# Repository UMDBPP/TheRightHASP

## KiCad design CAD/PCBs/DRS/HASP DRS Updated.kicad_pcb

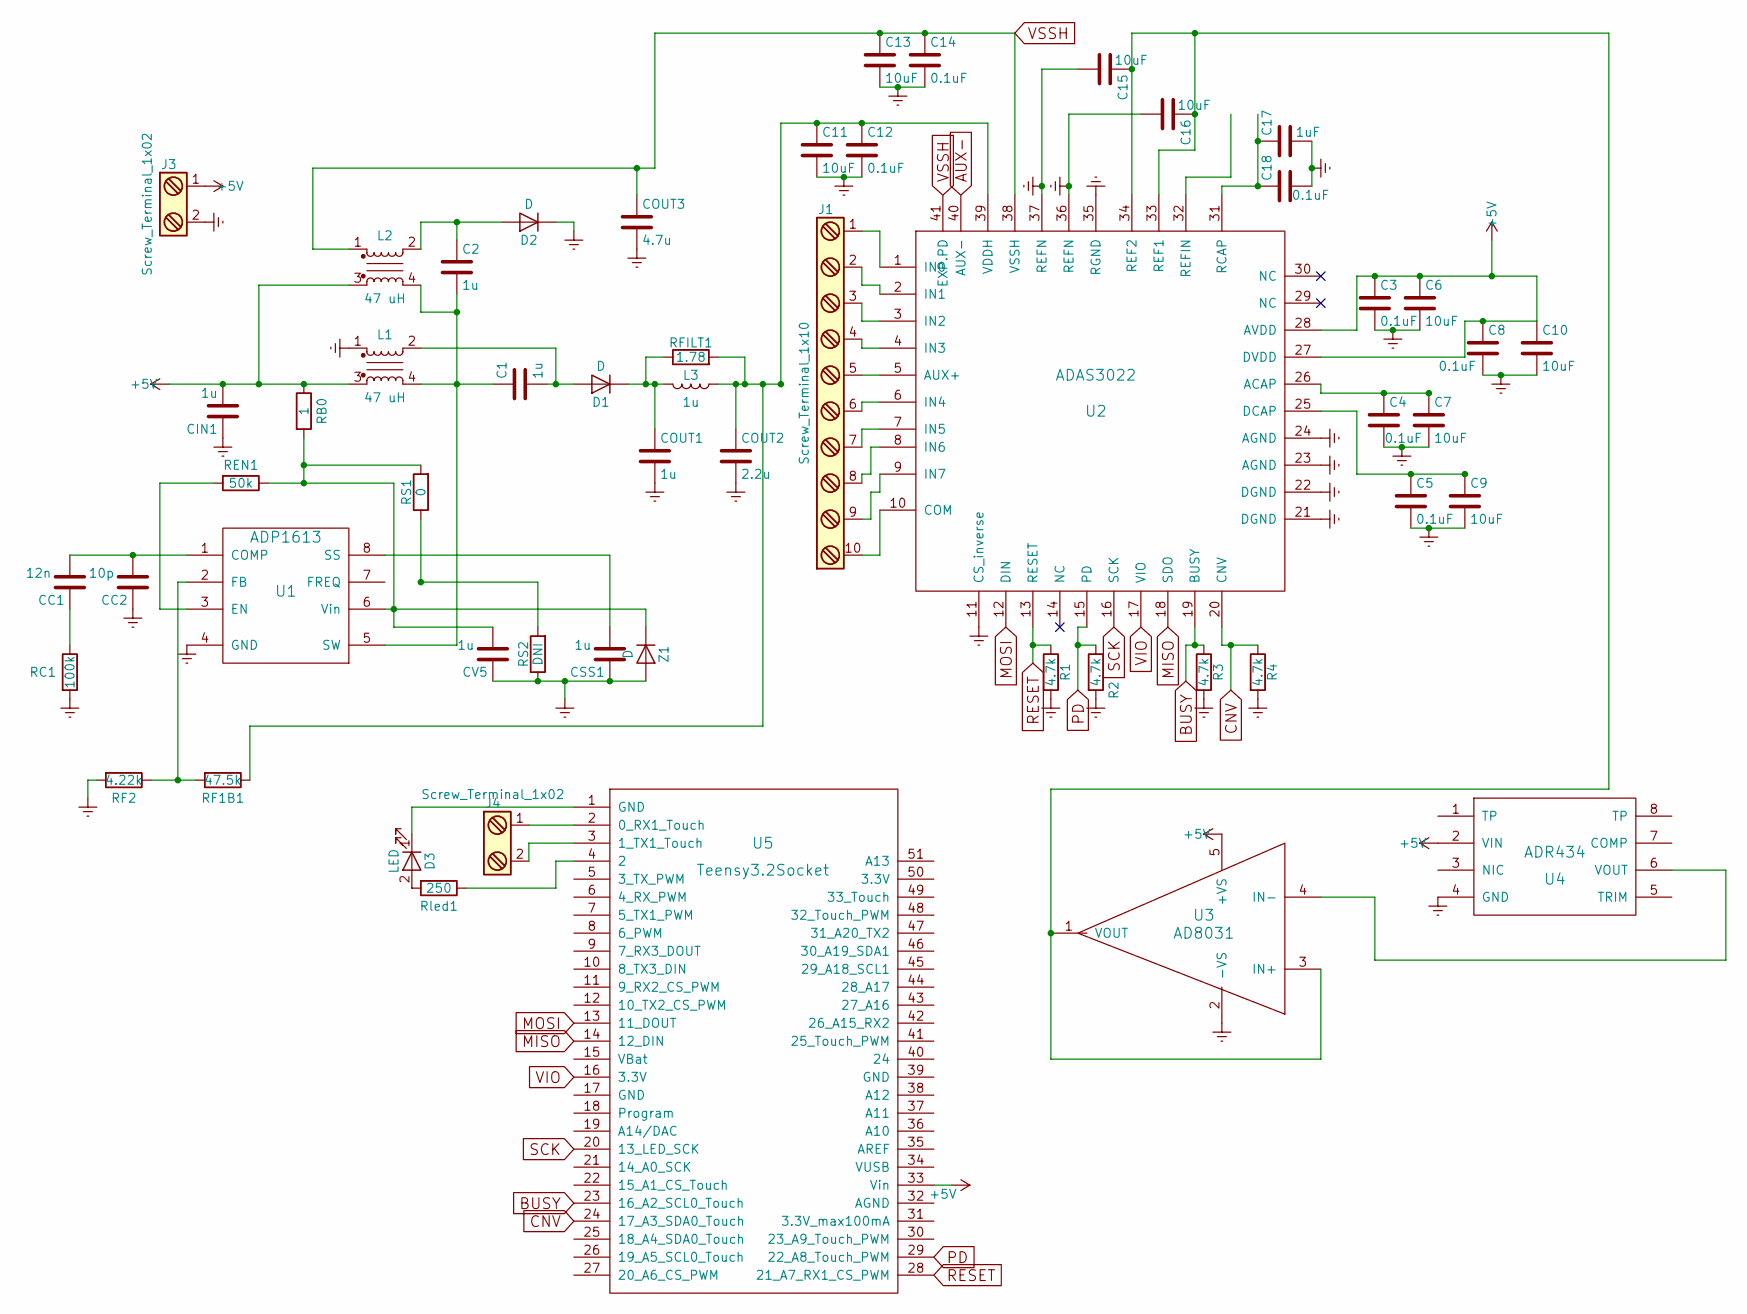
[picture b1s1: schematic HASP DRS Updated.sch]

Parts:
C1: 1u; C_0603
C2: 1u; C_0805
C3, C4, C5, C8, C12, C14, C18: 0.1uF; C_0603
C6, C7, C9, C10, C11, C13, C15, C16: 10uF; C_0603
C17: 1uF; C_0603
CC1: 12n; C_0603
CC2: 10p; C_0603
CIN1: 1u; C_0603
COUT1: 1u; C_0603
COUT2: 2.2u; C_1206
COUT3: 4.7u; C_1206
CSS1: 1u; C_0603
CV5: 1u; C_0603
D1, D2: D; D_SOT-23_ANK
D3: LED; LED_0603
J1: Screw_Terminal_1x10; TerminalBlock_Pheonix_MPT-2.54mm_10pol
J3, J4: Screw_Terminal_1x02; TerminalBlock_Pheonix_MPT-2.54mm_2pol
L1, L2: 47 uH; LPD5030-473MRB
L3: 1u; Neosid_Inductor_SM-NE30_SMD1210
R1, R2, R3, R4: 4.7k; R_0603
RB0: 1; R_0603
RC1: 100k; R_0603
REN1: 50k; R_0805
RF1B1: 47.5k; R_0603
RF2: 4.22k; R_0603
RFILT1: 1.78; R_0603
RS1: 0; R_0603
RS2: DNI; R_0603
Rled1: 250; R_0603
U1: ADP1613; SOP65P490X110-8N
U2: ADAS3022
U3: AD8031
U4: ADR434; SOIC127P600X175-8N
U5: Teensy3.2Socket
Z1: D; D_SOT-23_ANK

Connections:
AUX-: U2.40 (AUX-)
BUSY: R3.1, U2.19 (BUSY), U5.23 (16_A2_SCL0_Touch)
CNV: R4.1, U2.20 (CNV), U5.24 (17_A3_SDA0_Touch)
Earth: C3.2, C4.2, C5.2, C6.2, C7.2, C8.2, C9.2, C10.2, C11.2, C12.2, C13.2, C14.2, C15.2, C16.2, C17.2, C18.2, CC2.1, CIN1.1, COUT1.2, COUT2.2, COUT3.2, CSS1.1, CV5.1, D2.1 (K), J3.2, L1.1, R1.2, R2.2, R3.2, R4.2, RC1.2, RF2.2, RS2.1, U1.4 (GND), U2.11 (CS_inverse), U2.21 (DGND), U2.22 (DGND), U2.23 (AGND), U2.24 (AGND), U2.35 (RGND), U2.36 (REFN), U2.37 (REFN), U3.2 (-VS), U4.4 (GND), Z1.2 (A)
MISO: U2.18 (SDO), U5.14 (12_DIN)
MOSI: U2.12 (DIN), U5.13 (11_DOUT)
unnamed: C1.1, C2.2, L1.4, L2.4, U1.5 (SW)
unnamed: C1.2, D1.2 (A), L1.2
unnamed: C2.1, D2.2 (A), L2.2
unnamed: C4.1, C7.1, U2.26 (ACAP)
unnamed: C5.1, C9.1, U2.25 (DCAP)
unnamed: C11.1, C12.1, COUT2.1, L3.1, RF1B1.1, RFILT1.2, U2.39 (VDDH)
unnamed: C15.1, C16.1, U2.33 (REF1), U2.34 (REF2), U3.1 (VOUT), U3.3 (IN+)
unnamed: C17.1, C18.1, U2.31 (RCAP)
unnamed: CC1.1, RC1.1
unnamed: CC1.2, CC2.2, U1.1 (COMP)
unnamed: COUT1.1, D1.1 (K), L3.2, RFILT1.1
unnamed: CSS1.2, U1.8 (SS)
unnamed: CV5.2, RB0.2, REN1.1, RS1.2, U1.6 (Vin), Z1.1 (K)
unnamed: D3.1 (K), U5.1 (GND)
unnamed: D3.2 (A), Rled1.2
unnamed: J1.1, U2.1 (IN0)
unnamed: J1.2, U2.2 (IN1)
unnamed: J1.3, U2.3 (IN2)
unnamed: J1.4, U2.4 (IN3)
unnamed: J1.5, U2.5 (AUX+)
unnamed: J1.6, U2.6 (IN4)
unnamed: J1.7, U2.7 (IN5)
unnamed: J1.8, U2.8 (IN6)
unnamed: J1.9, U2.9 (IN7)
unnamed: J1.10, U2.10 (COM)
unnamed: J4.1, U5.2 (0_RX1_Touch)
unnamed: J4.2, U5.3 (1_TX1_Touch)
unnamed: REN1.2, U1.3 (EN)
unnamed: RF1B1.2, RF2.1, U1.2 (FB)
unnamed: RS1.1, RS2.2
unnamed: Rled1.1, U5.4 (2)
unnamed: U3.4 (IN-), U4.6 (VOUT)
PD: R2.1, U2.15 (PD), U5.29 (22_A8_Touch_PWM)
RESET: R1.1, U2.13 (RESET), U5.28 (21_A7_RX1_CS_PWM)
SCK: U2.16 (SCK), U5.20 (13_LED_SCK)
VIO: U2.17 (VIO), U5.16 (3.3V)
VSSH: C13.1, C14.1, COUT3.1, L2.1, U2.38 (VSSH), U2.41 (EXP.PD)

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
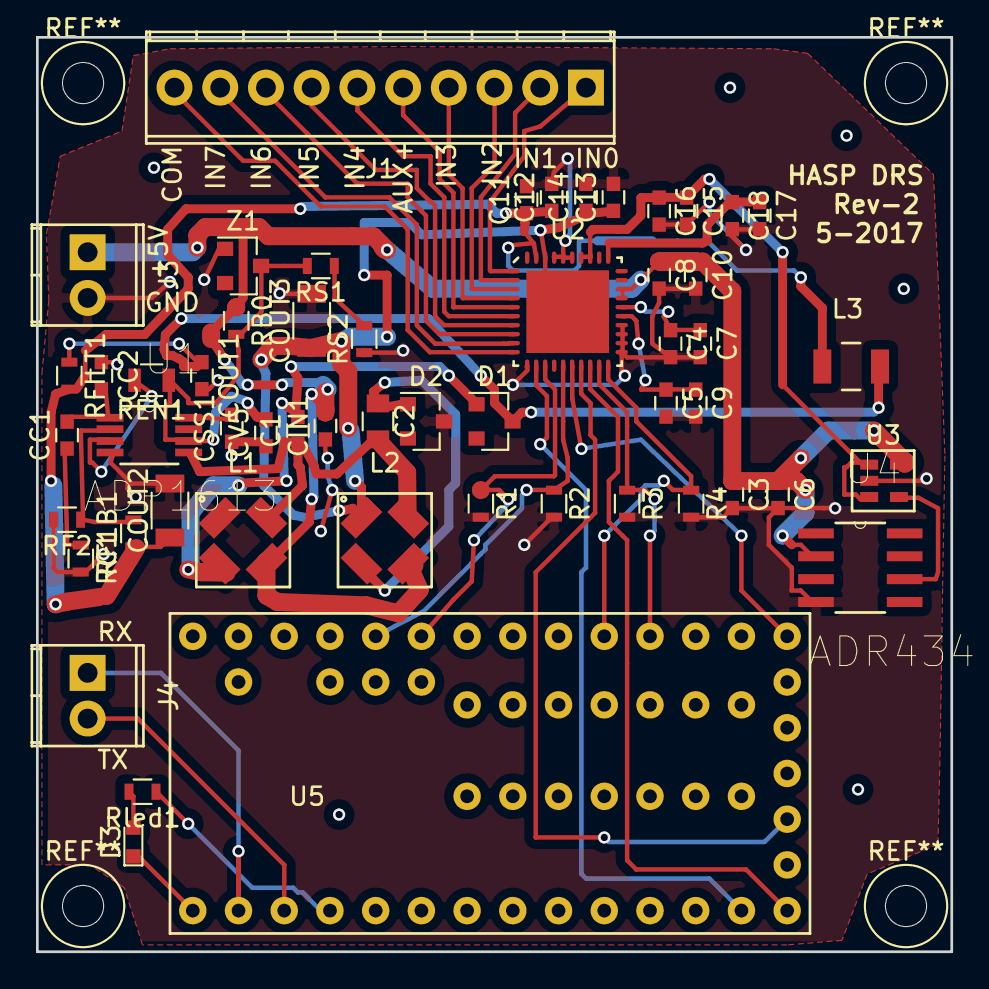
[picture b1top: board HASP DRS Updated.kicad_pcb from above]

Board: 2 copper layers, 50.8 x 50.8 mm, 54 parts (0 on the bottom side), 43 nets.

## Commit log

2017-07-31 Added Flight code for All HASP systems
2017-07-31 Un-commented logpkt function
2017-07-31 Added teensy check to serial downlink
2017-07-31 added folder for test loger
2017-07-31 serial format change
2017-08-02 usb code
2017-08-02 try two
2017-08-03 led and serial
2017-08-03 more changes
2017-08-03 lots of things
2017-08-03 Revert "led and serial"
    This reverts commit a8618d731beda92ef55c03ca48dbaeb55700c7cc.
2017-08-03 Revert "more changes"
    This reverts commit 580cdaa8f4b820441eea626d8264f035748e98ea.
2017-08-04 added serial downlink data
2017-08-04 post processing, second half
2017-08-04 ccsds sucks
2017-08-26 DRS sketch
2017-09-01 pi code
2017-09-01 rs232
2017-09-01 flight code, again
2017-09-01 flight code stuff
2017-09-02 Revert "Revert "led and serial""
    This reverts commit aec3f0d31d8a7807e8f7d2f3f65539eec9de71d4.
2017-09-02 Revert "Revert "Revert "led and serial"""
    This reverts commit a86a3a0b82a997fc37fdeea9c2a318c8b3a59739.
2017-09-27 added flush
2017-09-27 added serial uplink code
2017-09-27 welp
2018-04-04 2018cad
